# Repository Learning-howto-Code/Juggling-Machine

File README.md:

# Juggling-Machine
An automatic juggling machine, using a rpi pico, 2 nema 23 stepper motors and some python!

# PCB

# CAD

### Check out the video of the render here!
https://cdn.hackclub.com/019e38e4-be2f-7099-8626-64a2c3647a4a/juggling_machine_video.mp4

# Code
The main code is in main.py, with test scripts to make sure that each part is working first also inlcuded. I am not claiming credit for these, as they are opensource example code

# Bill of Materials

| Item | Unit Cost | Qty | Shipping | Full Cost | Link | Notes |
|------|-----------|-----|----------|-----------|------|-------|
| Stepper Motor | $17.80 | 2 | $16.50 | $54.20 | [NEMA 23 Bipolar](https://www.omc-stepperonline.com/nema-23-bipolar-1-8deg-1-26nm-178-4oz-in-2-8a-2-5v-57x57x56mm-4-wires-23hs22-2804s) | |
| Servo | N/A | 2 | $0.00 | $0.99 | [AliExpress](https://www.aliexpress.us/item/3256808303872992.html) | |
| 2020 Extrusion | 7 | 2 | $3.00 | $14 | [Aliexpress](https://www.aliexpress.us/item/3256803113028246.html?spm=a2g0o.productlist.main.4.926725ecmKHPrC&aem_p4p_detail=202606010914191761256831972900004179670&algo_pvid=e9001e90-323b-44cd-baa7-3bdbdfcf3629&algo_exp_id=e9001e90-323b-44cd-baa7-3bdbdfcf3629-3&pdp_ext_f=%7B%22order%22%3A%22404%22%2C%22eval%22%3A%221%22%2C%22fromPage%22%3A%22search%22%7D&pdp_npi=6%40dis%21USD%218.09%210.99%21%21%218.09%210.99%21%402101f11417803304593842669e0e08%2112000025092771406%21sea%21US%216415217639%21ABX%211%210%21n_tag%3A-29910%3Bd%3A7d30aa04%3Bm03_new_user%3A-29895%3BpisId%3A5000000207178484&curPageLogUid=lDMGDjOTO7JF&utparam-url=scene%3Asearch%7Cquery_from%3A%7Cx_object_id%3A1005003299342998%7C_p_origin_prod%3A&search_p4p_id=202606010914191761256831972900004179670_1) | |
| Motor Driver | N/A | 2 pack | $6.00 | $42.00 | [TMC5160 Pro v1.0](https://biqu.equipment/products/tmc5160-pro-v1-0?variant=40301980614754) | |
| Screws | N/A | — | — | — | — | Already have |
| RPi Pico | $5.00 | 1 | $12.00 | $11.00 | [LCSC](https://www.lcsc.com/product-detail/C41407547.html) | |
| Capacitor | $0.25 | 2 | — | $0.45 | [LCSC](https://www.lcsc.com/product-detail/C233122.html) | |
| Buck Converter | — | 1 | — | — | — | Already have |
| PCB | $4.00 | 1 | $3.00 | $7.50 | [JLCPCB](https://cart.jlcpcb.com/shopcart/cart/) | |
| | | | **Total** | **$134** | | |

*Claude formatted my BOM*

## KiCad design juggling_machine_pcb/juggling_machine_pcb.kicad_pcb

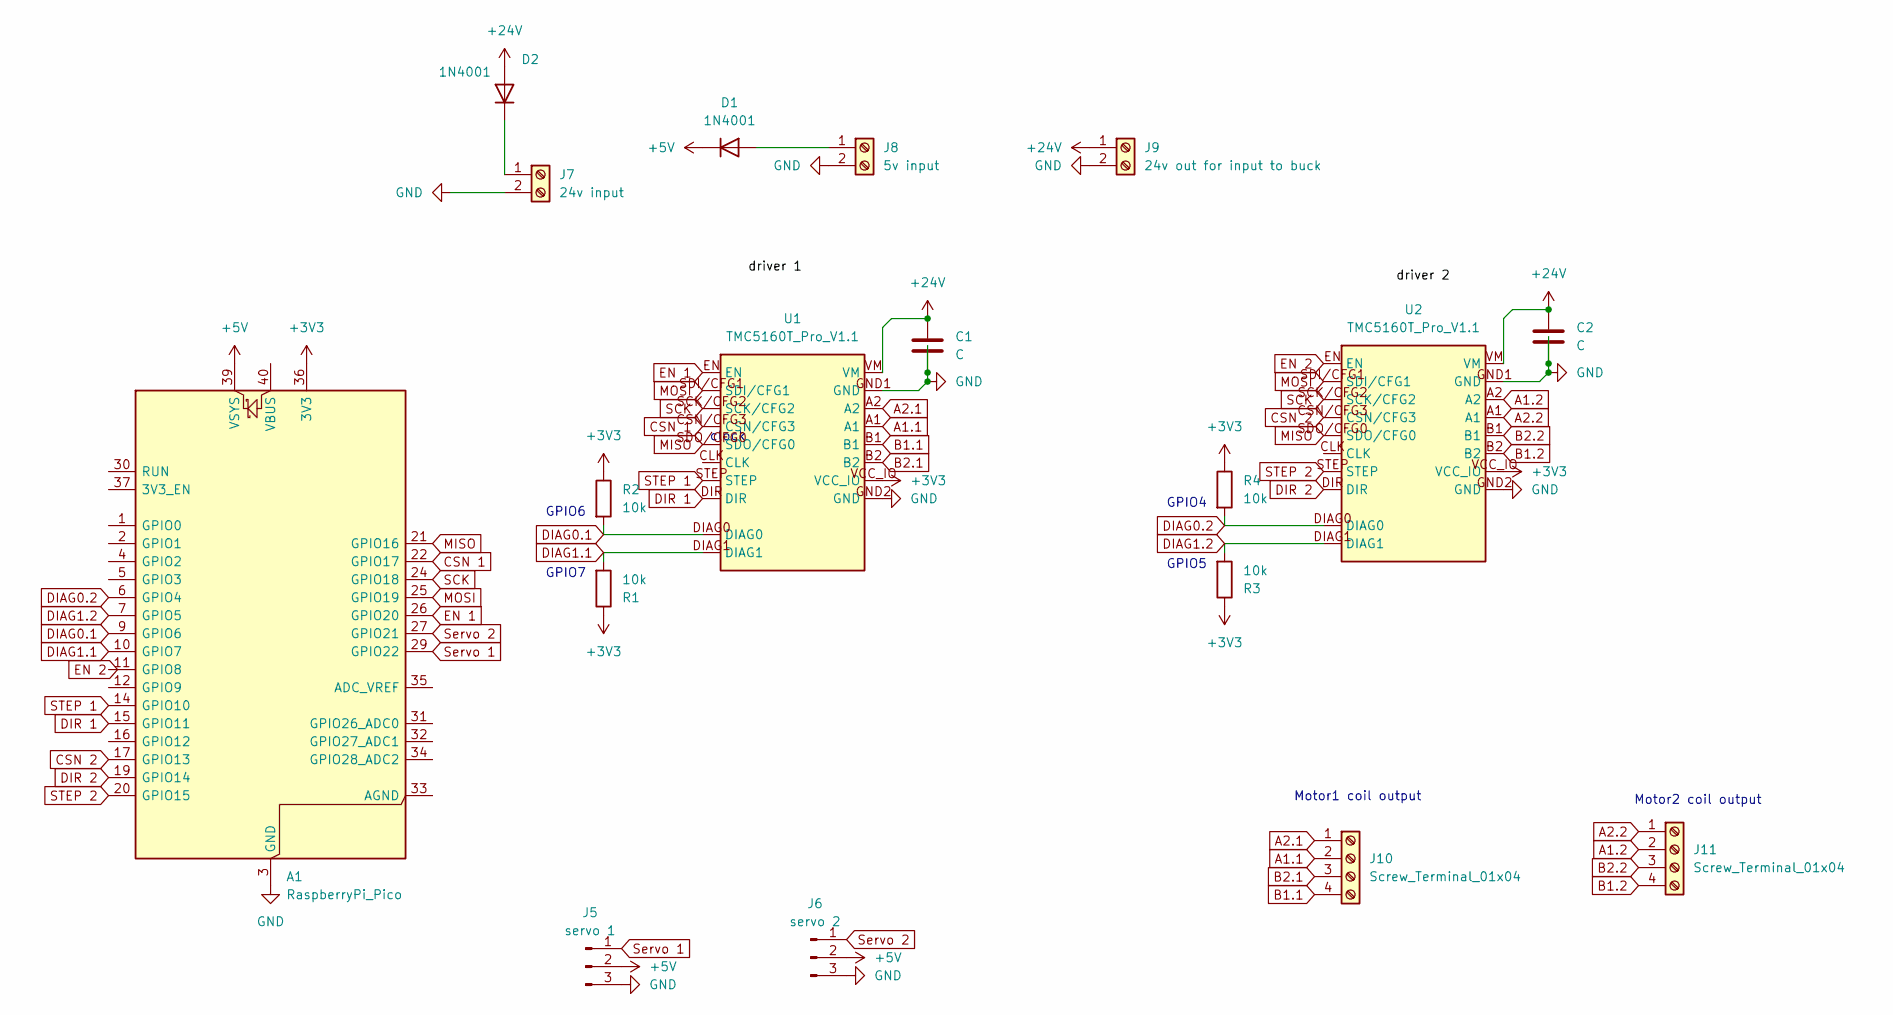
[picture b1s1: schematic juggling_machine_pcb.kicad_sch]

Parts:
A1: RaspberryPi_Pico; RaspberryPi_Pico_Common_Unspecified
C1, C2: C; CP_Radial_D6.3mm_P2.50mm
D1, D2: 1N4001; D_DO-41_SOD81_P10.16mm_Horizontal
J5: servo 1; PinHeader_1x03_P2.54mm_Vertical
J6: servo 2; PinHeader_1x03_P2.54mm_Vertical
J7: 24v input; TerminalBlock_Phoenix_MKDS-1,5-2_1x02_P5.00mm_Horizontal
J8: 5v input; TerminalBlock_Phoenix_MKDS-1,5-2_1x02_P5.00mm_Horizontal
J9: 24v out for input to buck; TerminalBlock_Phoenix_MKDS-1,5-2_1x02_P5.00mm_Horizontal
J10, J11: Screw_Terminal_01x04; TerminalBlock_4Ucon_1x04_P3.50mm_Horizontal
R1, R2, R3, R4: 10k; R_Axial_DIN0204_L3.6mm_D1.6mm_P5.08mm_Horizontal
U1, U2: TMC5160T_Pro_V1.1; BTT_TMC5160T_Pro_V1.1

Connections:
+3V3: A1.36 (3V3), R1.1, R2.1, R3.1, R4.1, U1.VCC_IO, U2.VCC_IO
+5V: A1.39 (VSYS), D1.1 (K), J5.2, J6.2
+24V: C1.1, C2.1, D2.2 (A), J9.1, U1.VM, U2.VM
A1.1: J10.2, U1.A1
A1.2: J11.2, U2.A2
A2.1: J10.1, U1.A2
A2.2: J11.1, U2.A1
B1.1: J10.4, U1.B1
B1.2: J11.4, U2.B2
B2.1: J10.3, U1.B2
B2.2: J11.3, U2.B1
CSN 1: A1.22 (GPIO17), U1.CSN/CFG3
CSN 2: A1.17 (GPIO13), U2.CSN/CFG3
DIAG0.1: A1.9 (GPIO6), R2.2, U1.DIAG0
DIAG0.2: A1.6 (GPIO4), R4.2, U2.DIAG0
DIAG1.1: A1.10 (GPIO7), R1.2, U1.DIAG1
DIAG1.2: A1.7 (GPIO5), R3.2, U2.DIAG1
DIR 1: A1.15 (GPIO11), U1.DIR
DIR 2: A1.19 (GPIO14), U2.DIR
EN 1: A1.26 (GPIO20), U1.EN
EN 2: U2.EN
GND: A1.3 (GND), A1.8 (GND), A1.13 (GND), A1.18 (GND), A1.23 (GND), A1.28 (GND), A1.38 (GND), C1.2, C2.2, J5.3, J6.3, J7.2, J8.2, J9.2, U1.GND1 (GND), U1.GND2 (GND), U2.GND1 (GND), U2.GND2 (GND)
MISO: A1.21 (GPIO16), U1.SDO/CFG0, U2.SDO/CFG0
MOSI: A1.25 (GPIO19), U1.SDI/CFG1, U2.SDI/CFG1
unnamed: D1.2 (A), J8.1
unnamed: D2.1 (K), J7.1
SCK: A1.24 (GPIO18), U1.SCK/CFG2, U2.SCK/CFG2
STEP 1: A1.14 (GPIO10), U1.STEP
STEP 2: A1.20 (GPIO15), U2.STEP
Servo 1: A1.29 (GPIO22), J5.1
Servo 2: A1.27 (GPIO21), J6.1

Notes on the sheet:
clock
Motor2 coil output
GPIO4
GPIO6
GPIO7
GPIO5
Motor1 coil output

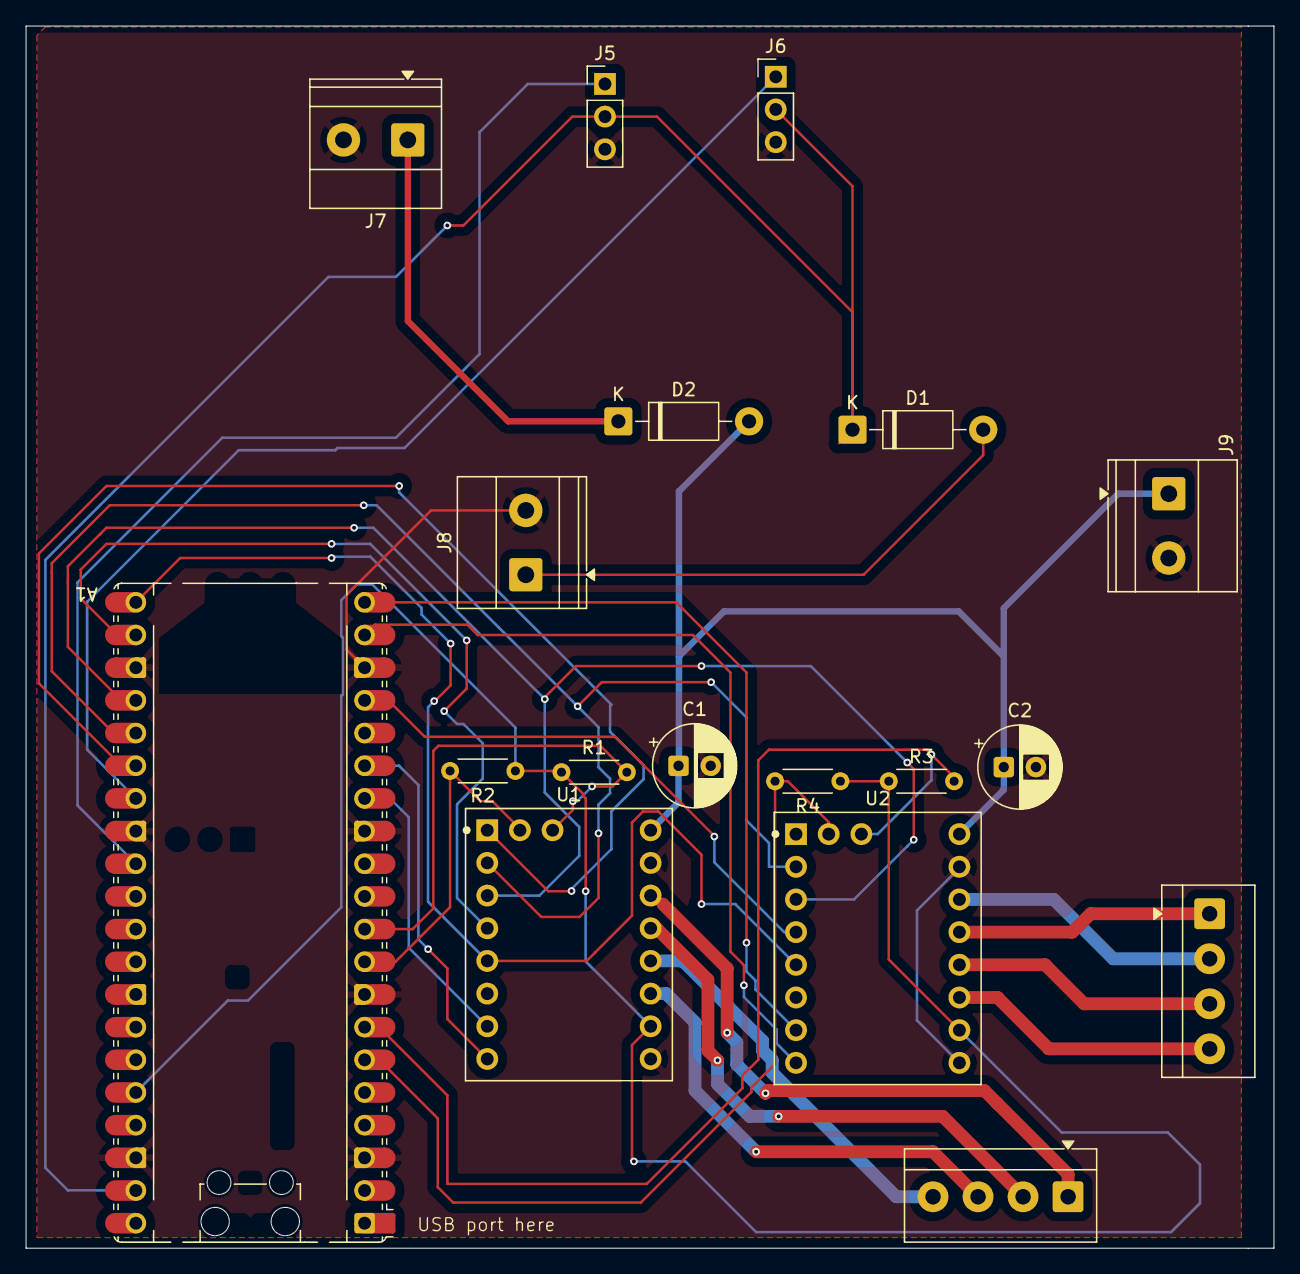
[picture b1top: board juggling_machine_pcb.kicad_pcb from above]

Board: 2 copper layers, 97.0 x 95.0 mm, 18 parts (0 on the bottom side), 30 nets.

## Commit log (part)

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2026-05-17 added pcb files, and video from cad render
2026-05-18 added step, stl, and f3z CAD files from fusion
2026-05-19 cobbling together a script from the wiki demo code, starting to understand the lib
2026-05-19 worked out full logic for code, also added test scripts for servos and stepper motors
2026-05-22 added bom and updated pcb
2026-05-22 filled out readme
2026-05-22 added note about video link
2026-05-29 added new BOM, plus updated pcb
2026-05-30 latest changes
2026-06-01 updated BOM with new 2020 supplier
2026-06-01 new BOM
2026-06-15 Fixed typo in bom total.
